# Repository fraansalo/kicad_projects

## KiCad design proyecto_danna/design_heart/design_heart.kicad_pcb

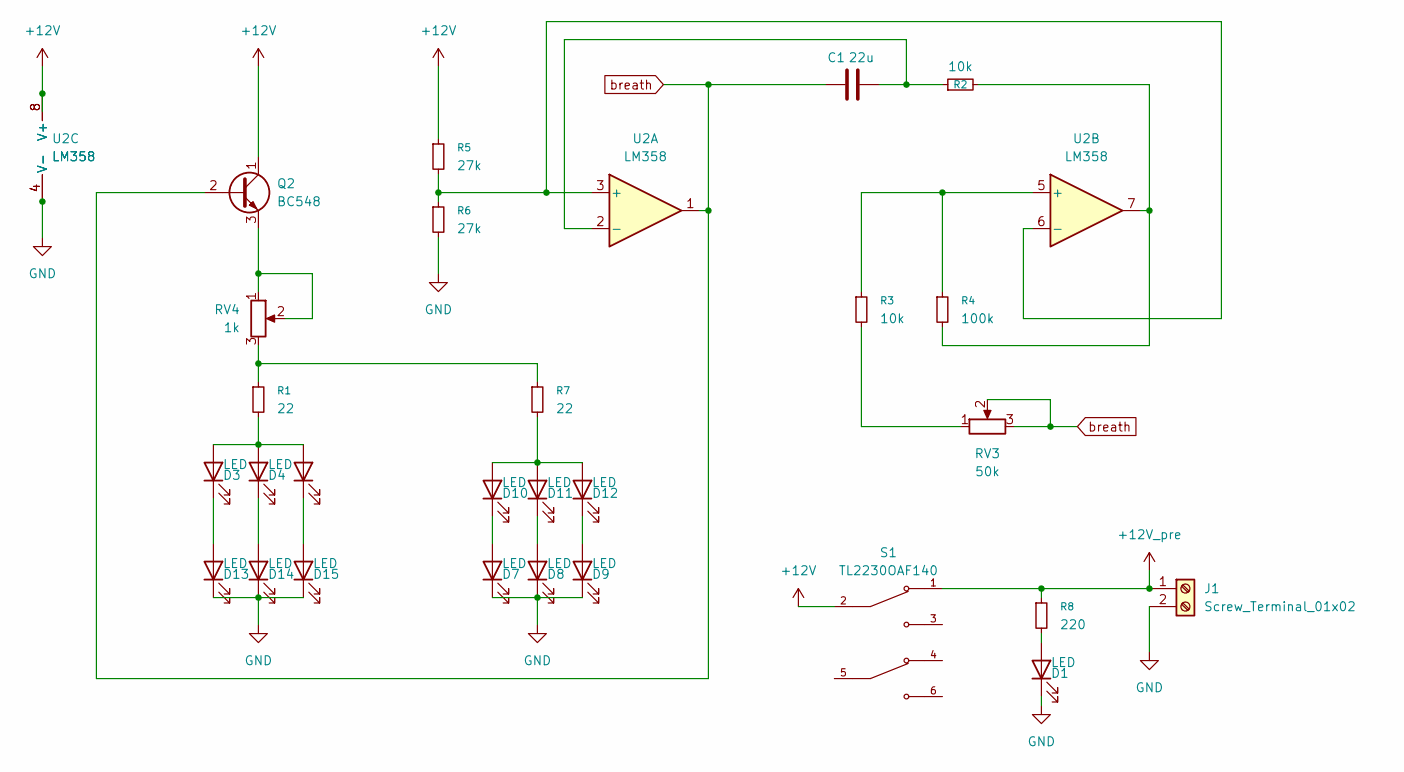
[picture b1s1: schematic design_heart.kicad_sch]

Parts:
C1: 22u; C_Radial_D8.0mm_H11.5mm_P3.50mm
D1, D3, D4, D5, D7, D8, D9, D10, D11, D12, D13, D14, D15: LED; LED_D5.0mm_IRGrey
J1: Screw_Terminal_01x02; TerminalBlock_MetzConnect_Type059_RT06302HBWC_1x02_P3.50mm_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
Q2: BC548; TO-92_Inline_Wide
R1, R7: 22; R_Axial_DIN0204_L3.6mm_D1.6mm_P7.62mm_Horizontal
R2, R3: 10k; R_Axial_DIN0204_L3.6mm_D1.6mm_P7.62mm_Horizontal
R4: 100k; R_Axial_DIN0204_L3.6mm_D1.6mm_P7.62mm_Horizontal
R5, R6: 27k; R_Axial_DIN0204_L3.6mm_D1.6mm_P7.62mm_Horizontal
R8: 220; R_Axial_DIN0204_L3.6mm_D1.6mm_P7.62mm_Horizontal
RV3: 50k; Potentiometer_ACP_CA9-V10_Vertical
RV4: 1k; Potentiometer_ACP_CA9-V10_Vertical
S1: TL2230OAF140; SW_TL2230OAF140; PARTREV E
U1: LM358
U2: LM358; DIP-8_W7.62mm_Socket

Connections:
+12V: Q2.1 (C), R5.1, S1.2, U1.8 (V+), U2.8 (V+)
+12V_pre: J1.1, R8.1, S1.1
GND: D1.1 (K), D7.1 (K), D8.1 (K), D9.1 (K), D13.1 (K), D14.1 (K), D15.1 (K), J1.2, R6.2, U1.4 (V-), U2.4 (V-)
unnamed: D1.2 (A), R8.2
unnamed: D3.2 (A), D4.2 (A), D5.2 (A), R1.2
unnamed: D10.2 (A), D11.2 (A), D12.2 (A), R7.2
unnamed: D7.2 (A), D10.1 (K)
unnamed: D8.2 (A), D11.1 (K)
unnamed: D9.2 (A), D12.1 (K)
unnamed: D3.1 (K), D13.2 (A)
unnamed: D4.1 (K), D14.2 (A)
unnamed: D5.1 (K), D15.2 (A)
unnamed: Q2.3 (E), RV4.1, RV4.2
unnamed: R1.1, R7.1, RV4.3
unnamed: R2.2, R4.2, U2.7
unnamed: R3.2, RV3.1
unnamed: R5.2, R6.1, U2.3 (+), U2.6 (-)
unnamed: C1.2, R2.1, U2.2 (-)
unnamed: R3.1, R4.1, U2.5 (+)
breath: C1.1, Q2.2 (B), RV3.2, RV3.3, U2.1

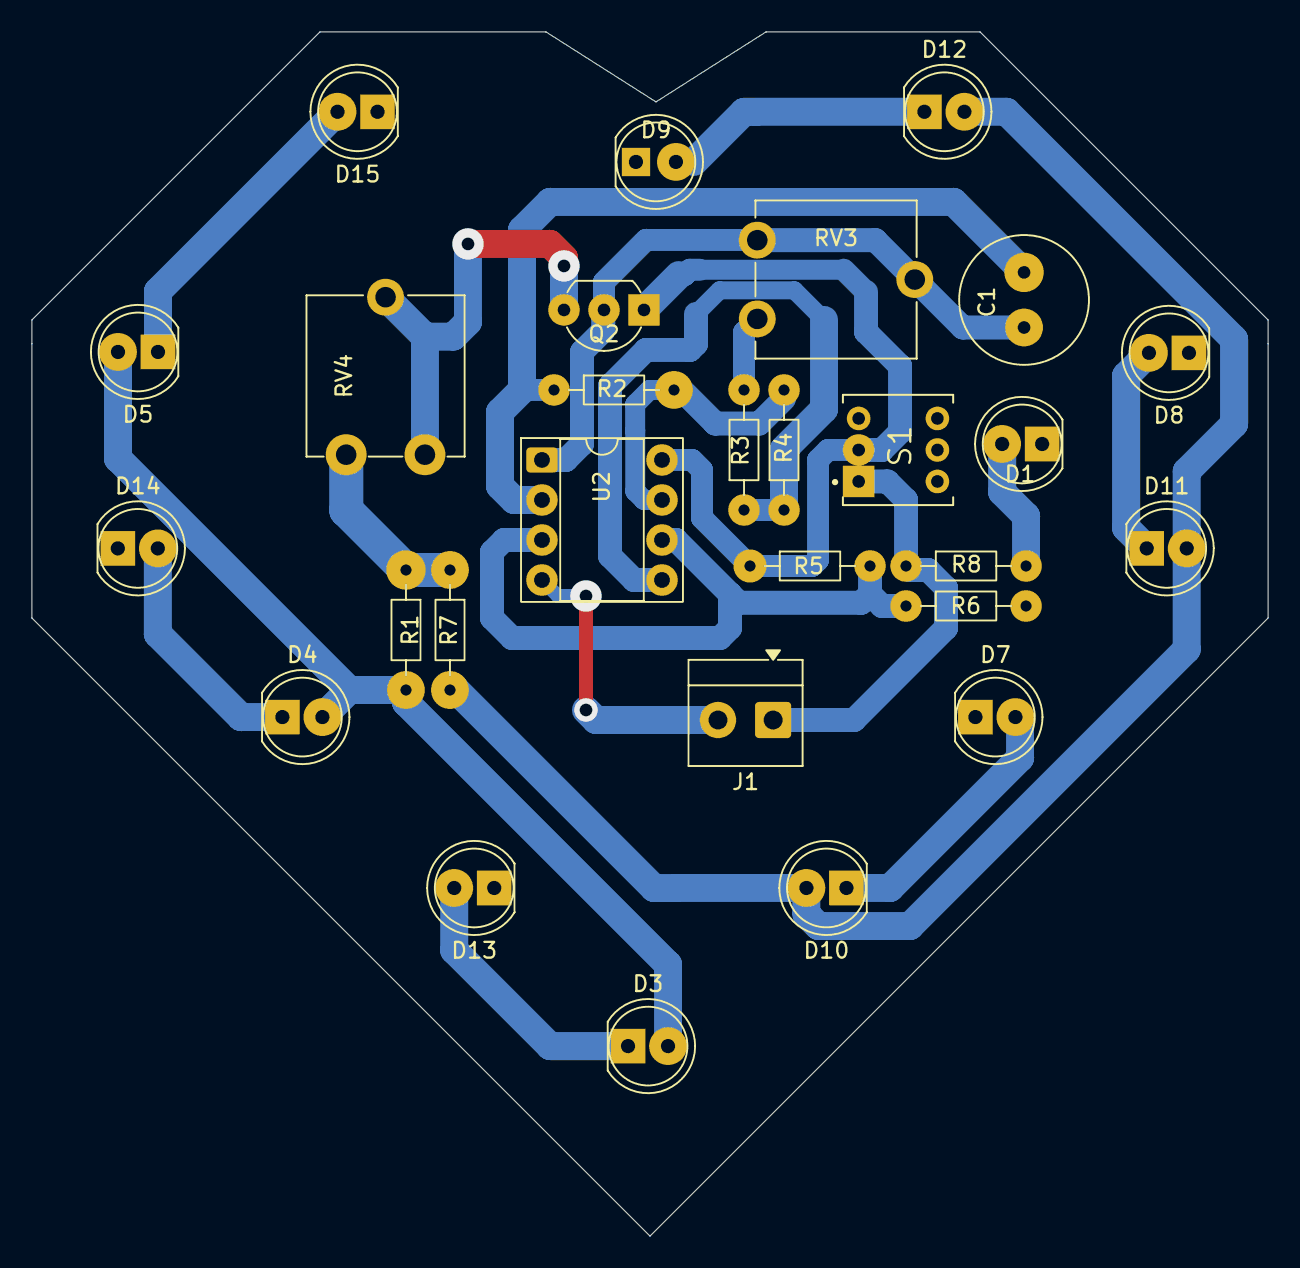
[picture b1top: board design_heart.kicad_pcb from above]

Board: 2 copper layers, 78.5 x 76.5 mm, 28 parts (0 on the bottom side), 20 nets.

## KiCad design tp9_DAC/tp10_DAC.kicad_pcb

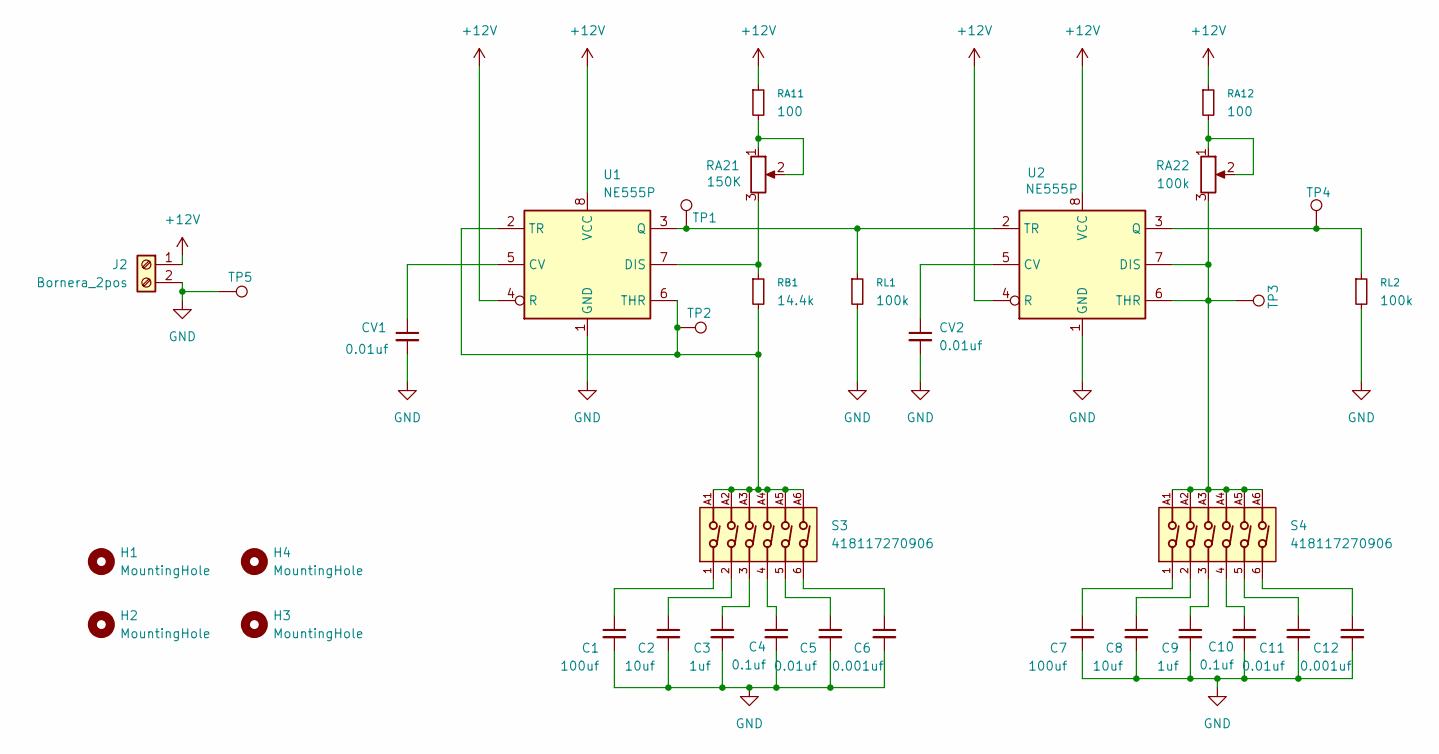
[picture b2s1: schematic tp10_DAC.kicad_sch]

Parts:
C1, C7: 100uf; C_Radial_D5.0mm_H11.0mm_P2.00mm
C2, C8: 10uf; C_Radial_D5.0mm_H11.0mm_P2.00mm
C3, C9: 1uf; C_Radial_D5.0mm_H11.0mm_P2.00mm
C4, C10: 0.1uf; C_Radial_D5.0mm_H11.0mm_P2.00mm
C5, C11: 0.01uf; C_Radial_D5.0mm_H11.0mm_P2.00mm
C6, C12: 0.001uf; C_Radial_D5.0mm_H11.0mm_P2.00mm
CV1, CV2: 0.01uf; C_Radial_D5.0mm_H11.0mm_P2.00mm
H1, H2, H3, H4: MountingHole; MountingHole_2.2mm_M2_DIN965
J2: Bornera_2pos; TerminalBlock_MetzConnect_Type011_RT05502HBLC_1x02_P5.00mm_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
RA11, RA12: 100; R_Axial_DIN0207_L6.3mm_D2.5mm_P10.16mm_Horizontal
RA21: 150K; Potentiometer_Alps_RK163_Single_Horizontal
RA22: 100k; Potentiometer_Alps_RK163_Single_Horizontal
RB1: 14.4k; R_Axial_DIN0207_L6.3mm_D2.5mm_P10.16mm_Horizontal
RL1, RL2: 100k; R_Axial_DIN0207_L6.3mm_D2.5mm_P10.16mm_Horizontal
S3, S4: 418117270906
TP1, TP2, TP3, TP4, TP5: TestPoint; TestPoint_THTPad_D1.0mm_Drill0.5mm
U1, U2: NE555P; DIP-8_W7.62mm

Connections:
+12V: J2.1, RA11.1, RA12.1, U1.4 (R), U1.8 (VCC), U2.4 (R), U2.8 (VCC); also elsewhere on the board
GND: C1.2, C2.2, C3.2, C4.2, C5.2, C6.2, C7.2, C8.2, C9.2, C10.2, C11.2, C12.2, CV1.2, CV2.2, J2.2, RL1.2, RL2.2, TP5.1, U1.1 (GND), U2.1 (GND); also elsewhere on the board
unnamed: C1.1, S3.1
unnamed: C2.1, S3.2
unnamed: C3.1, S3.3
unnamed: C4.1, S3.4
unnamed: C5.1, S3.5
unnamed: C6.1, S3.6
unnamed: C7.1, S4.1
unnamed: C8.1, S4.2
unnamed: C9.1, S4.3
unnamed: C10.1, S4.4
unnamed: C11.1, S4.5
unnamed: C12.1, S4.6
unnamed: RA11.2, RA21.1, RA21.2
unnamed: RA12.2, RA22.1, RA22.2
unnamed: CV1.1, U1.5 (CV)
unnamed: RA21.3, RB1.1, U1.7 (DIS)
unnamed: RL1.1, TP1.1, U1.3 (Q), U2.2 (TR)
unnamed: RB1.2, S3.A1, S3.A2, S3.A3, S3.A4, S3.A5, S3.A6, TP2.1, U1.1.8 (THR), U1.2 (TR), U1.6 (THR)
unnamed: CV2.1, U2.5 (CV)
unnamed: RA22.3, S4.A1, S4.A2, S4.A3, S4.A4, S4.A5, S4.A6, TP3.1, U2.6 (THR), U2.7 (DIS)
unnamed: RL2.1, TP4.1, U2.3 (Q)

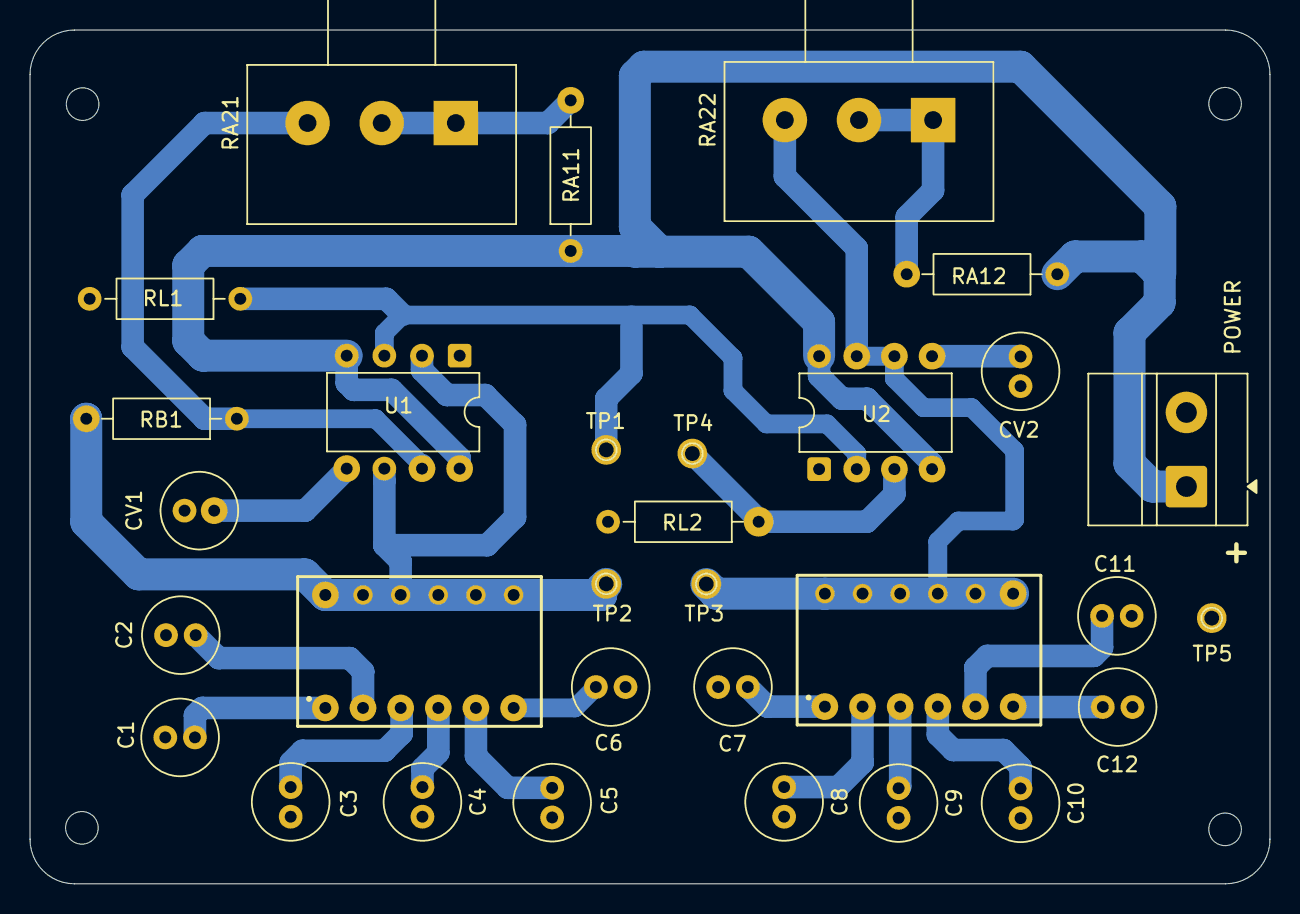
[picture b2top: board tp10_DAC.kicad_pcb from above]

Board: 2 copper layers, 83.7 x 57.6 mm, 35 parts (0 on the bottom side), 23 nets.

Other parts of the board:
POWER: BAT1; TerminalBlock_MetzConnect_Type011_RT05502HBLC_1x02_P5.00mm_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

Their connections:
+12V: POWER.1; also elsewhere on the board
GND: POWER.2; also elsewhere on the board

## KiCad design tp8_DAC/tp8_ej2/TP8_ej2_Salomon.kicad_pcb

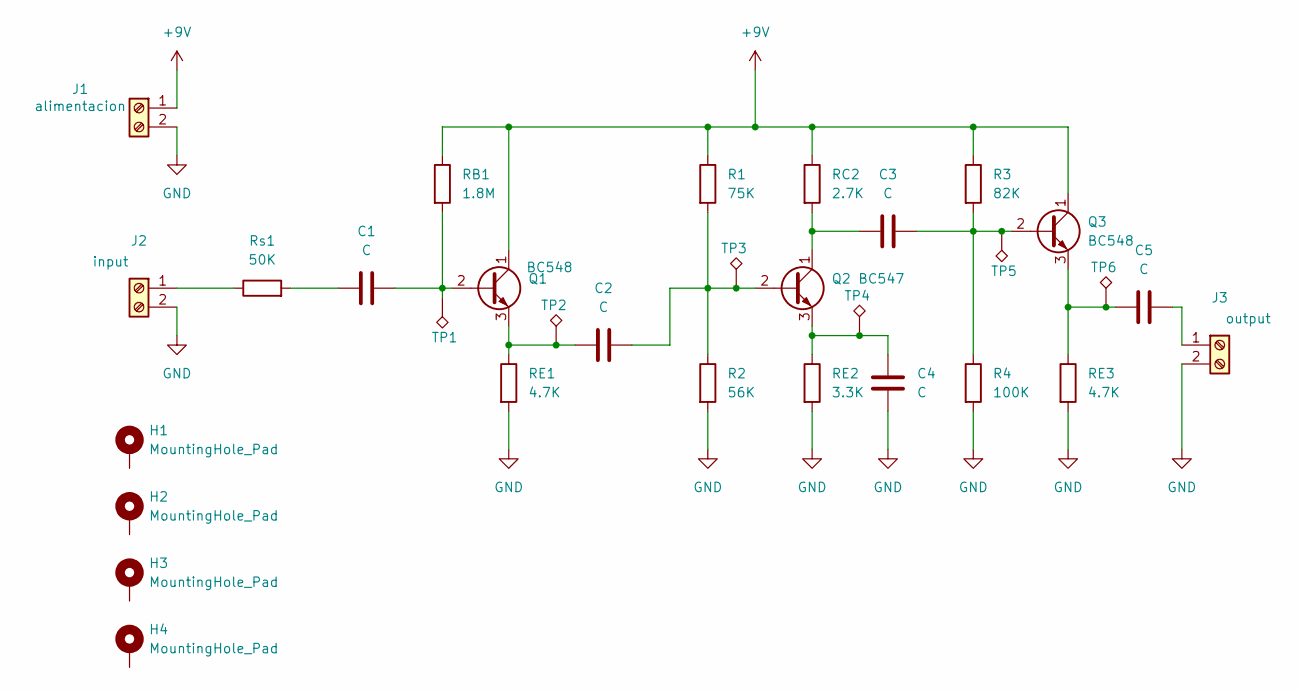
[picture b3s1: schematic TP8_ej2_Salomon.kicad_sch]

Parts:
C1, C2, C3, C4, C5: C; C_Disc_D5.0mm_W2.5mm_P2.50mm
H1, H2, H3, H4: MountingHole_Pad; MountingHole_2.2mm_M2_Pad_Via
J1: alimentacion; TerminalBlock_MaiXu_MX126-5.0-02P_1x02_P5.00mm
J2: input; TerminalBlock_MaiXu_MX126-5.0-02P_1x02_P5.00mm
J3: output; TerminalBlock_MaiXu_MX126-5.0-02P_1x02_P5.00mm
Q1, Q3: BC548; TO-92_Inline
Q2: BC547; TO-92_Inline
R1: 75K; R_Axial_DIN0204_L3.6mm_D1.6mm_P7.62mm_Horizontal
R2: 56K; R_Axial_DIN0204_L3.6mm_D1.6mm_P7.62mm_Horizontal
R3: 82K; R_Axial_DIN0204_L3.6mm_D1.6mm_P7.62mm_Horizontal
R4: 100K; R_Axial_DIN0204_L3.6mm_D1.6mm_P7.62mm_Horizontal
RB1: 1.8M; R_Axial_DIN0204_L3.6mm_D1.6mm_P7.62mm_Horizontal
RC2: 2.7K; R_Axial_DIN0204_L3.6mm_D1.6mm_P7.62mm_Horizontal
RE1, RE3: 4.7K; R_Axial_DIN0204_L3.6mm_D1.6mm_P7.62mm_Horizontal
RE2: 3.3K; R_Axial_DIN0204_L3.6mm_D1.6mm_P7.62mm_Horizontal
Rs1: 50K; R_Axial_DIN0204_L3.6mm_D1.6mm_P7.62mm_Horizontal
TP1, TP2, TP3, TP4, TP5, TP6: TestPoint_Alt; TestPoint_Keystone_5000-5004_Miniature

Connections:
+9V: J1.1, Q1.1 (C), Q3.1 (C), R1.1, R3.1, RB1.1, RC2.1; also elsewhere on the board
GND: C4.2, H1.1, H2.1, H3.1, H4.1, J1.2, J2.2, J3.2, R2.2, R4.2, RE1.2, RE2.2, RE3.2; also elsewhere on the board
unnamed: C1.1, Rs1.2
unnamed 3: J2.1, Rs1.1; also elsewhere on the board
unnamed 4: C5.2, J3.1; also elsewhere on the board
unnamed: C1.2, Q1.2 (B), RB1.2, TP1.1
unnamed: C2.1, Q1.3 (E), RE1.1, TP2.1
unnamed: C2.2, Q2.2 (B), R1.2, R2.1, TP3.1
unnamed: C3.1, Q2.1 (C), RC2.2
unnamed: C4.1, Q2.3 (E), RE2.1, TP4.1
unnamed: C3.2, Q3.2 (B), R3.2, R4.1, TP5.1
unnamed: C5.1, Q3.3 (E), RE3.1, TP6.1

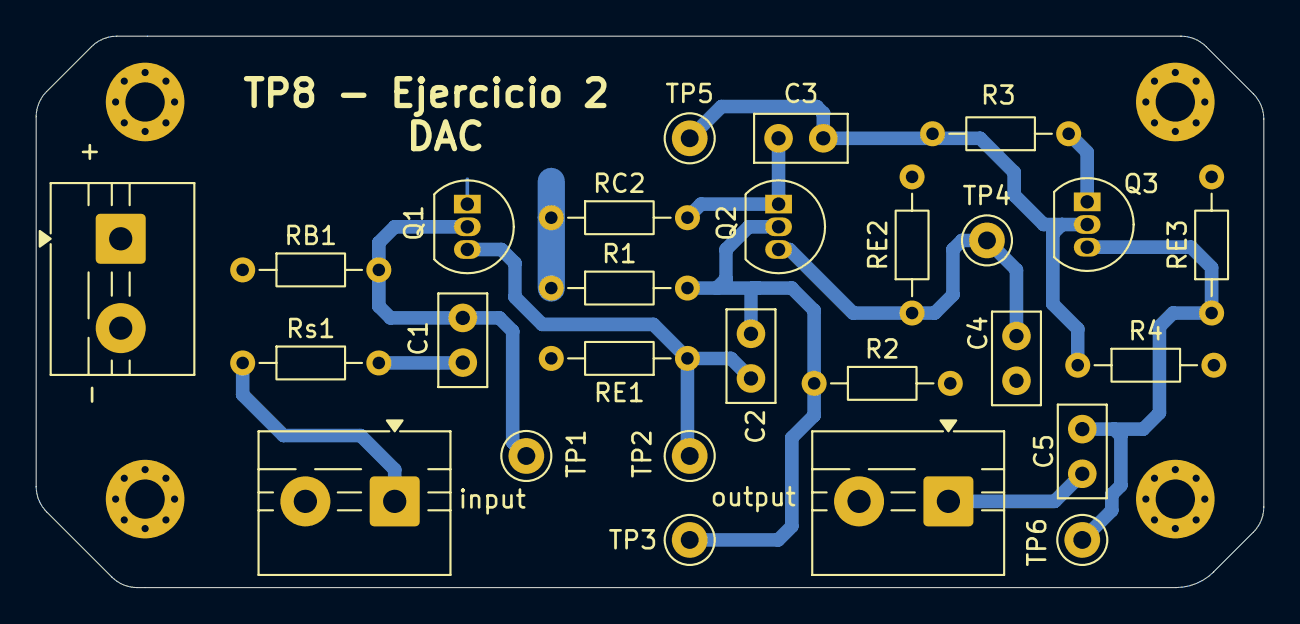
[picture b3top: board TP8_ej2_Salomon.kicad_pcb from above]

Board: 2 copper layers, 68.7 x 30.9 mm, 31 parts (1 on the bottom side), 12 nets.

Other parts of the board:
+: alimentacion; TerminalBlock_MaiXu_MX126-5.0-02P_1x02_P5.00mm
input: input; TerminalBlock_MaiXu_MX126-5.0-02P_1x02_P5.00mm
output: output; TerminalBlock_MaiXu_MX126-5.0-02P_1x02_P5.00mm

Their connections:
+9V: +.1; also elsewhere on the board
GND: +.2, input.2, output.2; also elsewhere on the board
unnamed 3: input.1; also elsewhere on the board
unnamed 4: output.1; also elsewhere on the board

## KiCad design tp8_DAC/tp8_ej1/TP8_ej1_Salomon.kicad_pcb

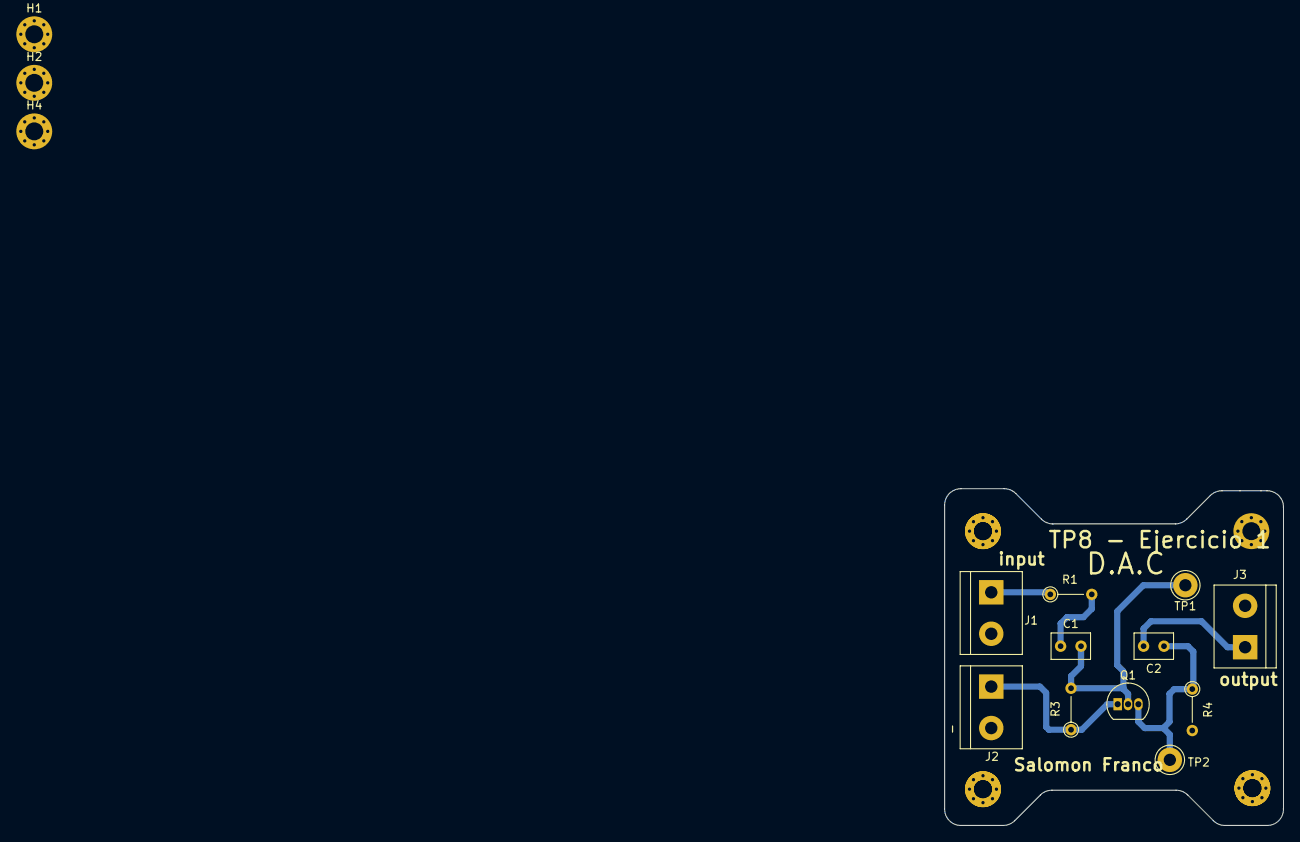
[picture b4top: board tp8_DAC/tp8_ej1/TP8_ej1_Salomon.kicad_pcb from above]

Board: 2 copper layers, 41.5 x 41.3 mm, 18 parts (0 on the bottom side), 7 nets.

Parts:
C1, C2: C; C_Rect_L4.6mm_W3.0mm_P2.50mm_MKS02_FKP02
H1, H2, H3, H3#2, H3#3, H3#4, H4: MountingHole_Pad; MountingHole_2.2mm_M2_Pad_Via
J1: Input_signal; TerminalBlock_bornier-2_P5.08mm
J2: alimentacion; TerminalBlock_bornier-2_P5.08mm
J3: output_signal; TerminalBlock_bornier-2_P5.08mm
Q1: BC548; TO-92_Inline
R1: Rs; R_Axial_DIN0204_L3.6mm_D1.6mm_P5.08mm_Vertical
R3: RB; R_Axial_DIN0204_L3.6mm_D1.6mm_P5.08mm_Vertical
R4: RE; R_Axial_DIN0204_L3.6mm_D1.6mm_P5.08mm_Vertical
TP1: TestPoint_Alt; Pin_D1.3mm_L11.0mm_LooseFit
TP2: Pin_D1.3mm_L11.0mm_LooseFit

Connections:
GND: H3#2.1, H3#3.1, H3#4.1, J1.2, J2.2, J3.2, R4.2
unnamed: C1.1, R1.2
unnamed: J1.1, R1.1
unnamed: C2.2, J3.1
unnamed: C1.2, Q1.2 (B), R3.2, TP1.1
unnamed: C2.1, Q1.3 (E), R4.1, TP2.1
VDD: J2.1, Q1.1 (C), R3.1

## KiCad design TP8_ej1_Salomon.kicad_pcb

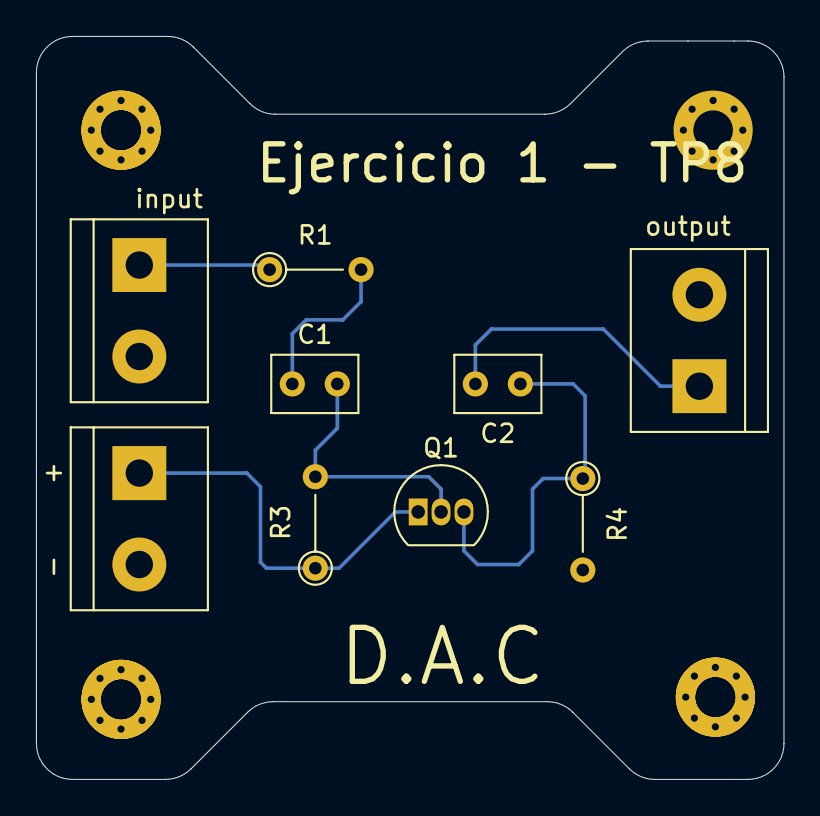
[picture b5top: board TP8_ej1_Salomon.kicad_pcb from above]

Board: 2 copper layers, 41.5 x 41.3 mm, 13 parts (0 on the bottom side), 7 nets.

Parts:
+: alimentacion; TerminalBlock_bornier-2_P5.08mm
C1, C2: C; C_Rect_L4.6mm_W3.0mm_P2.50mm_MKS02_FKP02
H3, H3#2, H3#3, H3#4: MountingHole_Pad; MountingHole_2.2mm_M2_Pad_Via
Q1: BC548; TO-92_Inline
R1: Rs; R_Axial_DIN0204_L3.6mm_D1.6mm_P5.08mm_Vertical
R3: RB; R_Axial_DIN0204_L3.6mm_D1.6mm_P5.08mm_Vertical
R4: RE; R_Axial_DIN0204_L3.6mm_D1.6mm_P5.08mm_Vertical
input: Input_signal; TerminalBlock_bornier-2_P5.08mm
output: output_signal; TerminalBlock_bornier-2_P5.08mm

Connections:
GND: +.2, H3.1, H3#2.1, H3#3.1, H3#4.1, R4.2, input.2, output.2
unnamed: C1.1, R1.2
unnamed: R1.1, input.1
unnamed: C2.2, output.1
unnamed: C1.2, Q1.2 (B), R3.2
unnamed: C2.1, Q1.3 (E), R4.1
VDD: +.1, Q1.1 (C), R3.1

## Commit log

2025-10-06 update_schematics_ej1
2025-10-06 pusheo_prueba_1
2025-10-06 git_ignore
2025-10-07 update_schematics_ej2
2025-10-07 test_gitignore
2025-10-08 update_final
2025-10-08 retoque_final
2025-10-28 update_tp10_DAC
2025-10-28 update_tp9_DAC
2025-10-30 update_tp9_pcb
2025-10-31 modelos_step
2025-10-31 entrega_tp10
2025-11-07 gerber_files
2025-11-09 update_PCB
2025-11-11 retoques_cnc
2025-11-18 silkscreen
2025-12-05 heart_proyect
2025-12-09 update_heart
2025-12-11 update_pcb_puentes
2025-12-11 nuevo_layout
2025-12-22 retoques
2026-01-21 avance
